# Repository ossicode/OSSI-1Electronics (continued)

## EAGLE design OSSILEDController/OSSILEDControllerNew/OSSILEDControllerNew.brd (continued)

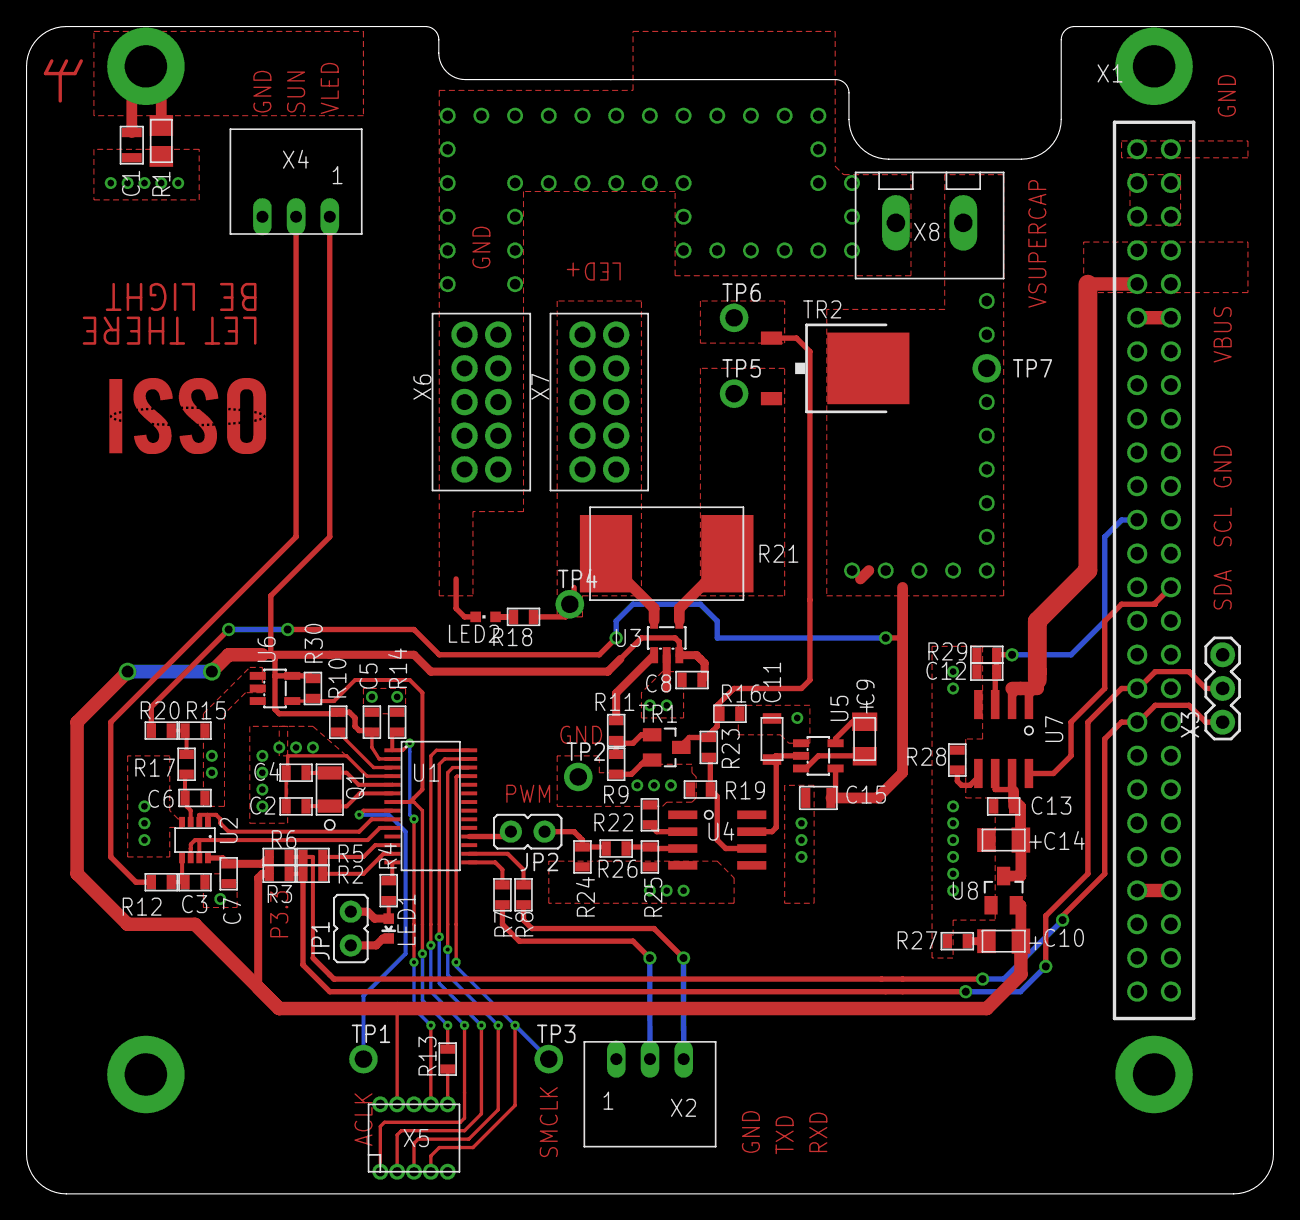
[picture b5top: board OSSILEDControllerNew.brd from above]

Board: 2 copper layers, 94.0 x 88.0 mm, 80 parts (0 on the bottom side), 54 nets.

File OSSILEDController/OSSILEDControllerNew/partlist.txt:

Partlist

Exported from OSSILEDControllerNew.sch at 2013-02-26 ¿ÀÈÄ 1:47:38

EAGLE Version 6.1.0 Copyright (c) 1988-2012 CadSoft

Assembly variant: 

Part     Value                Device             Package              Library  Sheet

C1                            C0805(2012)        C0805(2012)          OSSI     1
C2       12.5pF               C0603(1608)        C0603(1608)          OSSI     2
C3       100nF                C0603(1608)        C0603(1608)          OSSI     2
C4       12.5pF               C0603(1608)        C0603(1608)          OSSI     2
C5       100nF                C0603(1608)        C0603(1608)          OSSI     2
C6       100nF                C0603(1608)        C0603(1608)          OSSI     2
C7       100nF                C0603(1608)        C0603(1608)          OSSI     2
C8       100nF                C0603(1608)        C0603(1608)          OSSI     2
C9       10uF, LDO Tantal 16V C-TANTAL-A         C1206(3216)-A        OSSI     2
C10      10uF, LDO Tantal 16V C-TANTAL-A         C1206(3216)-A        OSSI     2
C11      1206 Cap             C1206(3216)-GCM31  C1206-GCM31          OSSI     2
C12      1uF                  C0603(1608)        C0603(1608)          OSSI     2
C13      100nF                C0603(1608)        C0603(1608)          OSSI     2
C14      10uF, LDO Tantal 16V C-TANTAL-A         C1206(3216)-A        OSSI     2
C15      1uF 0805             C0805(2012)        C0805(2012)          OSSI     2
H1       MOUNT-PAD-ROUND3.2   MOUNT-PAD-ROUND3.2 3.2-PAD-ROUND        OSSI     1
H2       MOUNT-PAD-ROUND3.2   MOUNT-PAD-ROUND3.2 3.2-PAD-ROUND        OSSI     1
H3       MOUNT-PAD-ROUND3.2   MOUNT-PAD-ROUND3.2 3.2-PAD-ROUND        OSSI     1
H4       MOUNT-PAD-ROUND3.2   MOUNT-PAD-ROUND3.2 3.2-PAD-ROUND        OSSI     1
JP1                           JP1Q               JP1                  OSSI     2
JP2                           JP1Q               JP1                  OSSI     2
LED1                          LED0603            LED-0603             SparkFun 2
LED2                          LEDCHIPLED_0603    CHIPLED_0603         led      2
Q1       NX-3215              NX-3215            NX-3215              OSSI     2
R1       511                  RWSL1206           WSL1206              OSSI     1
R2       250                  R0603(1608)        R0603(1608)          OSSI     2
R3       10k                  R0603(1608)        R0603(1608)          OSSI     2
R4       1k                   R0603(1608)        R0603(1608)          OSSI     2
R5       250                  R0603(1608)        R0603(1608)          OSSI     2
R6       10k                  R0603(1608)        R0603(1608)          OSSI     2
R7       4.7k                 R0603(1608)        R0603(1608)          OSSI     2
R8       4.7k                 R0603(1608)        R0603(1608)          OSSI     2
R9       6.2k                 R0603(1608)        R0603(1608)          OSSI     2
R10      TBD                  R0603(1608)        R0603(1608)          OSSI     2
R11      9.1k                 R0603(1608)        R0603(1608)          OSSI     2
R12      1k                   R0603(1608)        R0603(1608)          OSSI     2
R13      4.7k                 R0603(1608)        R0603(1608)          OSSI     2
R14      47k                  R0603(1608)        R0603(1608)          OSSI     2
R15      100k                 R0603(1608)        R0603(1608)          OSSI     2
R16      DNP                  R0603(1608)        R0603(1608)          OSSI     2
R17      1k                   R0603(1608)        R0603(1608)          OSSI     2
R18      1.5k                 R0603(1608)        R0603(1608)          OSSI     2
R19      2.2k                 R0603(1608)        R0603(1608)          OSSI     2
R20      100k                 R0603(1608)        R0603(1608)          OSSI     2
R21      0.005, 2W RSENSE     RWSR2              R4527(12070)         OSSI     2
R22      1.1k                 R0603(1608)        R0603(1608)          OSSI     2
R23      100k                 R0603(1608)        R0603(1608)          OSSI     2
R24      100k                 R0603(1608)        R0603(1608)          OSSI     2
R25                           R0603(1608)        R0603(1608)          OSSI     2
R26      1.5k                 R0603(1608)        R0603(1608)          OSSI     2
R27      0                    R0603(1608)        R0603(1608)          OSSI     2
R28      TBD                  R0603(1608)        R0603(1608)          OSSI     2
R29      100k                 R0603(1608)        R0603(1608)          OSSI     2
R30      100k                 R0603(1608)        R0603(1608)          OSSI     2
TP1      TP                   TP                 TP-13                OSSI     2
TP2      TP                   TP                 TP-13                OSSI     2
TP3      TP                   TP                 TP-13                OSSI     2
TP4      TP                   TP                 TP-13                OSSI     2
TP5      TP                   TP                 TP-13                OSSI     2
TP6      TP                   TP                 TP-13                OSSI     2
TP7      TP                   TP                 TP-13                OSSI     2
TR1      FDV301N              FDV301N            SOT23                OSSI     2
TR2      FDD8896              FDD8896            TO252                OSSI     2
U1       MSP430F2132          MSP430F2132        PW28                 OSSI     2
U2       OPA2347              OPA2347            SOT23-8DCN           OSSI     2
U3       MAX4376              MAX4376            SOT23-5DBV           OSSI     2
U4       LM7321               LM7321             SO8                  OSSI     2
U5       MAX1682              MAX1682            SOT23-5DBV           OSSI     2
U6       TPS3838              TPS3838            SOT23-5DBV           OSSI     2
U7       MAX890L              MAX890L            SO8                  OSSI     2
U8       MCP1700_SOT23        MCP1700_SOT23      SOT23                OSSI     2
X1       ESQ-126-38-G-D       ESQ-126-38-G-D     ESQ-126-XX-X-D       OSSI     1
X2       5268-03              5268-03            5268-03              OSSI     2
X3                            M03PTH             1X03                 OSSI     2
X4       5268-03              5268-03            5268-03              OSSI     2
X5       JTAG10PINMINI-H      JTAG10PINMINI-H    M50-3200545          OSSI     2
X6       ICCON_POWERCON       ICCON_POWERCON     ICCON6643220-1       OSSI     2
X7       ICCON_POWERCON       ICCON_POWERCON     ICCON6643220-1       OSSI     2
X8       WEIDMULLER           WEIDMULLER         WEIDMULLER1760490000 OSSI     2

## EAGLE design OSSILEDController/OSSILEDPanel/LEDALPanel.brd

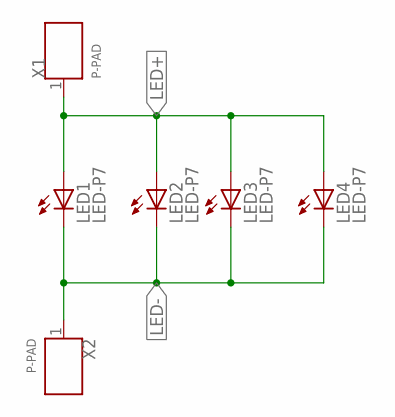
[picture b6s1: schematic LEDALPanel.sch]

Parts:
LED1, LED2, LED3, LED4: LED-P7; P7
X1, X2: P-PAD

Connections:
LED+: LED1.A, LED2.A, LED3.A, LED4.A, X1.1
LED-: LED1.C, LED2.C, LED3.C, LED4.C, X2.1

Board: 2 copper layers, 6 parts (0 on the bottom side), 2 nets, no tracks yet.

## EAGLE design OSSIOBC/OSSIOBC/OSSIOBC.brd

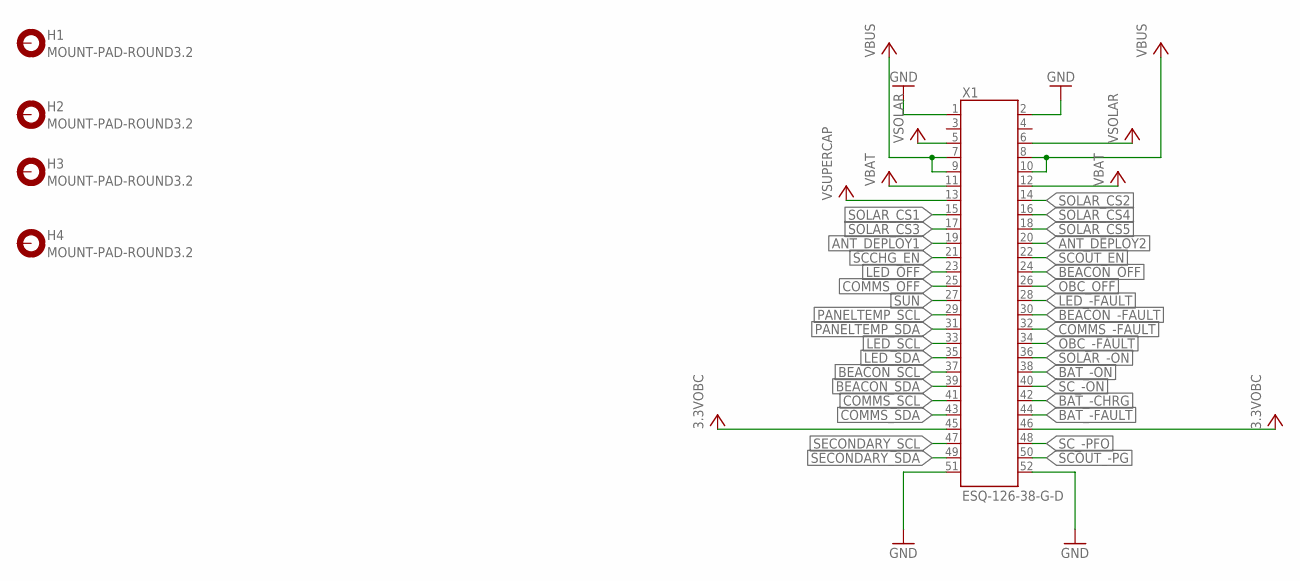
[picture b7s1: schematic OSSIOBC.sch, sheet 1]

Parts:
H1, H2, H3, H4: MOUNT-PAD-ROUND3.2; 3.2-PAD-ROUND
X1: ESQ-126-38-G-D; ESQ-126-XX-X-D

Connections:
3.3VOBC: X1.45, X1.46; also elsewhere on the board
ANT_DEPLOY1: X1.19; also elsewhere on the board
ANT_DEPLOY2: X1.20; also elsewhere on the board
BAT_-CHRG: X1.42; also elsewhere on the board
BAT_-FAULT: X1.44; also elsewhere on the board
BAT_-ON: X1.38; also elsewhere on the board
BEACON_-FAULT: X1.30; also elsewhere on the board
BEACON_OFF: X1.24; also elsewhere on the board
BEACON_SCL: X1.37; also elsewhere on the board
BEACON_SDA: X1.39; also elsewhere on the board
COMMS_-FAULT: X1.32; also elsewhere on the board
COMMS_OFF: X1.25; also elsewhere on the board
COMMS_SCL: X1.41; also elsewhere on the board
COMMS_SDA: X1.43; also elsewhere on the board
GND: X1.1, X1.2, X1.51, X1.52; also elsewhere on the board
LED_-FAULT: X1.28; also elsewhere on the board
LED_OFF: X1.23; also elsewhere on the board
LED_SCL: X1.33; also elsewhere on the board
LED_SDA: X1.35; also elsewhere on the board
OBC_-FAULT: X1.34; also elsewhere on the board
OBC_OFF: X1.26; also elsewhere on the board
PANELTEMP_SCL: X1.29; also elsewhere on the board
PANELTEMP_SDA: X1.31; also elsewhere on the board
SCCHG_EN: X1.21; also elsewhere on the board
SCOUT_-PG: X1.50; also elsewhere on the board
SCOUT_EN: X1.22; also elsewhere on the board
SC_-ON: X1.40; also elsewhere on the board
SC_-PFO: X1.48; also elsewhere on the board
SECONDARY_SCL: X1.47; also elsewhere on the board
SECONDARY_SDA: X1.49; also elsewhere on the board
SOLAR_-ON: X1.36; also elsewhere on the board
SOLAR_CS1: X1.15; also elsewhere on the board
SOLAR_CS2: X1.14; also elsewhere on the board
SOLAR_CS3: X1.17; also elsewhere on the board
SOLAR_CS4: X1.16; also elsewhere on the board
SOLAR_CS5: X1.18; also elsewhere on the board
SUN: X1.27; also elsewhere on the board
VBAT: X1.11, X1.12; also elsewhere on the board
VBUS: X1.7, X1.8, X1.9, X1.10; also elsewhere on the board
VSOLAR: X1.5, X1.6; also elsewhere on the board
VSUPERCAP: X1.13; also elsewhere on the board

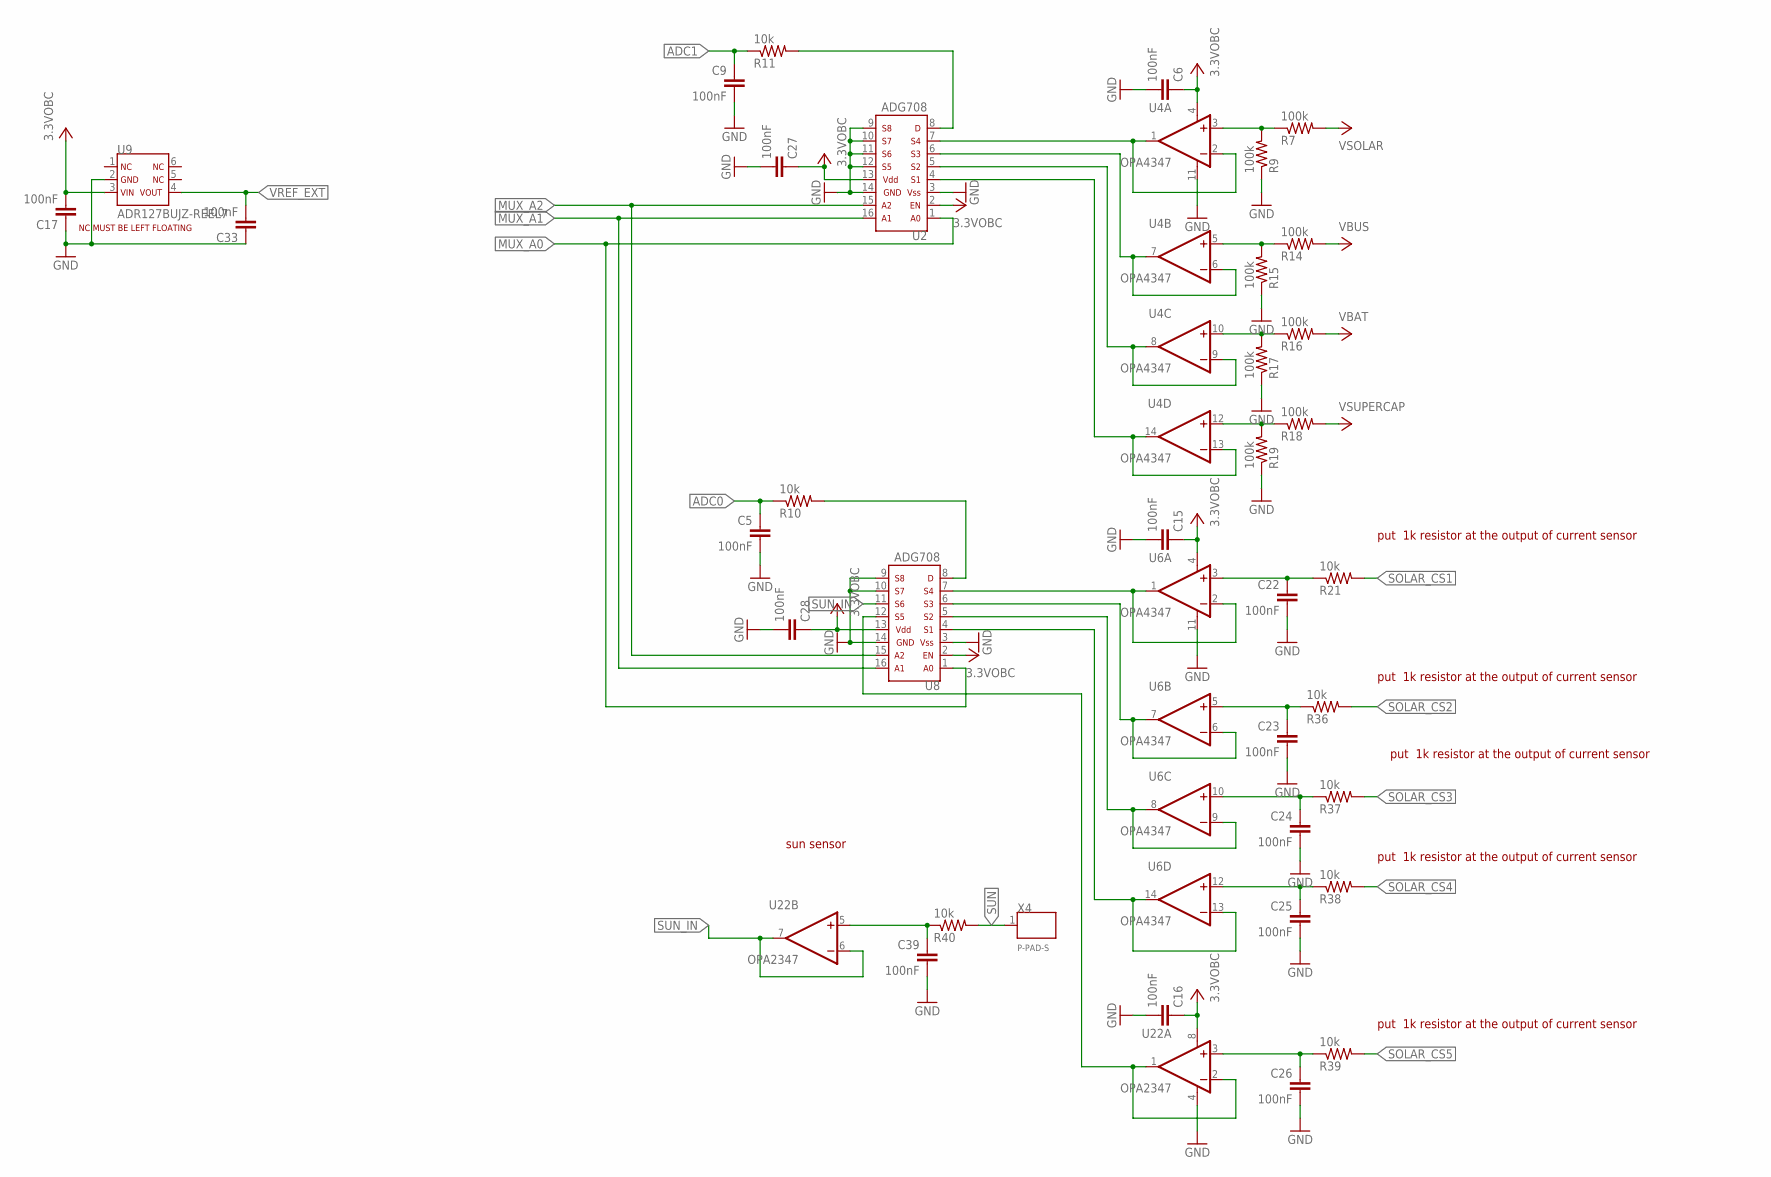
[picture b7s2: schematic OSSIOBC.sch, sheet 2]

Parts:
C5, C6, C9, C15, C16, C17, C22, C23, C24, C25, C26, C27, C28, C33, C39: 100nF; C0603(1608)
R7, R9, R14, R15, R16, R17, R18, R19: 100k; R0603(1608)
R10, R11, R21, R36, R37, R38, R39, R40: 10k; R0603(1608)
U2, U8: ADG708; TSSOP16-RU
U4, U6: OPA4347; TSSOP14-PW
U9: ADR127BUJZ-REEL7; TSOT-6UJ-6
U22: OPA2347; SOT23-8DCN
X4: P-PAD-S

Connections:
3.3VOBC: C6.1, C15.1, C16.1, C17.2, C27.1, C28.1, U2.2, U2.13, U4.4 (V+), U6.4 (V+), U8.2, U8.13, U9.3, U22.8 (V+); also elsewhere on the board
ADC0: C5.1, R10.1; also elsewhere on the board
ADC1: C9.1, R11.1; also elsewhere on the board
GND: C5.2, C6.2, C9.2, C15.2, C16.2, C17.1, C22.2, C23.2, C24.2, C25.2, C26.2, C27.2, C28.2, C33.1, C39.2, R9.1, R15.1, R17.1, R19.1, U2.3, U2.9, U2.10, U2.11, U2.12, U2.14, U4.11 (V-), U6.11 (V-), U8.3, U8.9, U8.10, U8.14, U9.2, U22.4 (V-); also elsewhere on the board
MUX_A0: U2.1, U8.1; also elsewhere on the board
MUX_A1: U2.16, U8.16; also elsewhere on the board
MUX_A2: U2.15, U8.15; also elsewhere on the board
unnamed: R7.1, R9.2, U4.3 (+IN)
unnamed: U2.7, U4.1 (OUT), U4.2 (-IN)
unnamed: U2.6, U4.6 (-IN), U4.7 (OUT)
unnamed: U2.5, U4.8 (OUT), U4.9 (-IN)
unnamed: U2.4, U4.13 (-IN), U4.14 (OUT)
unnamed: U6.1 (OUT), U6.2 (-IN), U8.7
unnamed: U6.6 (-IN), U6.7 (OUT), U8.6
unnamed: R14.1, R15.2, U4.5 (+IN)
unnamed: R16.1, R17.2, U4.10 (+IN)
unnamed: R18.1, R19.2, U4.12 (+IN)
unnamed: R11.2, U2.8
unnamed: U6.8 (OUT), U6.9 (-IN), U8.5
unnamed: R10.2, U8.8
unnamed: U6.13 (-IN), U6.14 (OUT), U8.4
unnamed: U8.12, U22.1 (OUT), U22.2 (-IN)
unnamed: C22.1, R21.1, U6.3 (+IN)
unnamed: C23.1, R36.1, U6.5 (+IN)
unnamed: C24.1, R37.1, U6.10 (+IN)
unnamed: C25.1, R38.1, U6.12 (+IN)
unnamed: C26.1, R39.1, U22.3 (+IN)
unnamed: C39.1, R40.1, U22.5 (+IN)
SOLAR_CS1: R21.2; also elsewhere on the board
SOLAR_CS2: R36.2; also elsewhere on the board
SOLAR_CS3: R37.2; also elsewhere on the board
SOLAR_CS4: R38.2; also elsewhere on the board
SOLAR_CS5: R39.2; also elsewhere on the board
SUN: R40.2, X4.1; also elsewhere on the board
SUN_IN: U8.11, U22.6 (-IN), U22.7 (OUT)
VBAT: R16.2; also elsewhere on the board
VBUS: R14.2; also elsewhere on the board
VREF_EXT: C33.2, U9.4; also elsewhere on the board
VSOLAR: R7.2; also elsewhere on the board
VSUPERCAP: R18.2; also elsewhere on the board

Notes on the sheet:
put 1k resistor at the output of current sensor
sun sensor

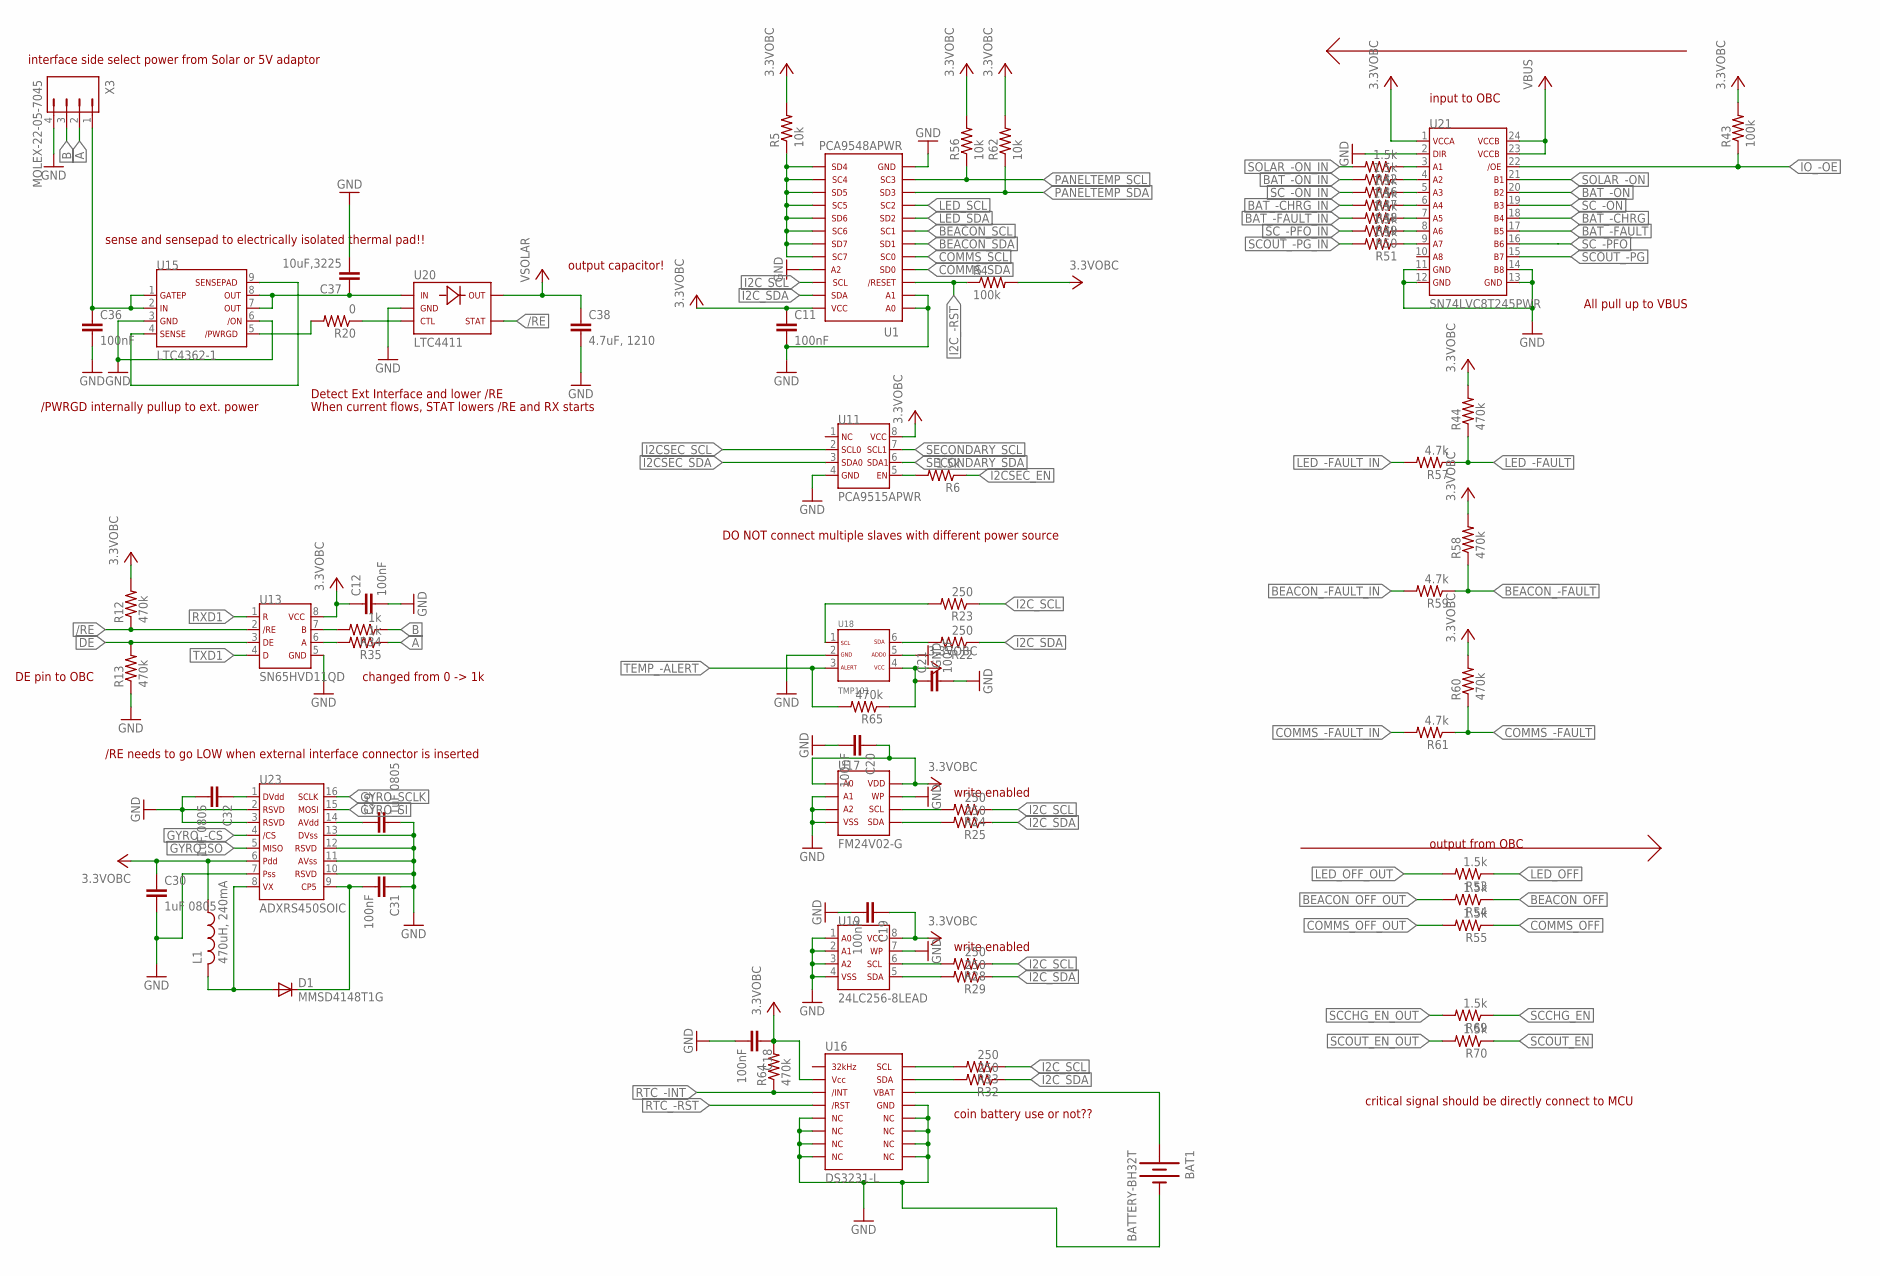
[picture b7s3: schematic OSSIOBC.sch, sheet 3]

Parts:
BAT1: BATTERY-BH32T; BH32T-C-G
C11, C12, C18, C19, C20, C21, C31, C36: 100nF; C0603(1608)
C29, C30, C32: 1uF 0805; C0805(2012)
C37: 10uF,3225; C1210-GCM32
C38: 4.7uF, 1210; C1206-GCM31
D1: MMSD4148T1G; SOD-123
L1: 470uH, 240mA; L(2220)
R4, R43: 100k; R0603(1608)
R5, R56, R62: 10k; R0603(1608)
R6, R42, R46, R47, R48, R49, R50, R51, R53, R54, R55, R69, R70: 1.5k; R0603(1608)
R12, R13, R44, R58, R60, R64, R65: 470k; R0603(1608)
R20: 0; R0603(1608)
R22, R23, R24, R25, R28, R29, R32, R33: 250; R0603(1608)
R34, R35: 1k; R0603(1608)
R57, R59, R61: 4.7k; R0603(1608)
U1: PCA9548APWR; TSSOP-24-PW
U11: PCA9515APWR; TSSOP-8
U13: SN65HVD11QD; SO8
U15: LTC4362-1; DFN8-2X3
U16: DS3231-L; SO16L
U17: FM24V02-G; SO8
U18: TMP101; SOT23-6DBV
U19: 24LC256-8LEAD; SO08-208
U20: LTC4411; TSOT23-5
U21: SN74LVC8T245PWR; PW_R-PDSO-G24
U23: ADXRS450SOIC; SOIC-16CAV
X3: MOLEX-22-05-7045; 22-05-7045

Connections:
3.3VOBC: C11.1, C12.1, C18.1, C19.1, C20.1, C21.1, C30.1, L1.P$1 (1), R4.2, R5.2, R12.2, R43.2, R44.2, R56.2, R58.2, R60.2, R62.2, R64.2, R65.1, U1.24, U11.8, U13.8, U16.2, U17.1 (A0), U17.8 (VDD), U18.4, U19.8, U21.1, U23.6; also elsewhere on the board
/RE: R12.1, U13.2, U20.P$4
A: R35.1, X3.2
B: R34.1, X3.3
BAT_-CHRG: U21.18; also elsewhere on the board
BAT_-CHRG_IN: R48.2; also elsewhere on the board
BAT_-FAULT: U21.17; also elsewhere on the board
BAT_-FAULT_IN: R49.2; also elsewhere on the board
BAT_-ON: U21.20; also elsewhere on the board
BAT_-ON_IN: R46.2; also elsewhere on the board
BEACON_-FAULT: R58.1, R59.1; also elsewhere on the board
BEACON_-FAULT_IN: R59.2; also elsewhere on the board
BEACON_OFF: R54.1; also elsewhere on the board
BEACON_OFF_OUT: R54.2; also elsewhere on the board
BEACON_SCL: U1.7; also elsewhere on the board
BEACON_SDA: U1.6; also elsewhere on the board
COMMS_-FAULT: R60.1, R61.1; also elsewhere on the board
COMMS_-FAULT_IN: R61.2; also elsewhere on the board
COMMS_OFF: R55.1; also elsewhere on the board
COMMS_OFF_OUT: R55.2; also elsewhere on the board
COMMS_SCL: U1.5; also elsewhere on the board
COMMS_SDA: U1.4; also elsewhere on the board
DE: R13.2, U13.3; also elsewhere on the board
GND: BAT1.N (-), C11.2, C12.2, C18.2, C19.2, C20.2, C21.2, C29.2, C30.2, C31.1, C32.2, C36.2, C37.P$2 (2), C38.P$2 (2), R13.1, U1.1, U1.2, U1.12, U1.21, U11.4, U13.5, U15.3, U15.6, U16.5, U16.6, U16.7, U16.8, U16.9, U16.10, U16.11, U16.12, U16.13, U17.2 (A1), U17.3 (A2), U17.4 (VSS), U17.7 (WP), U18.2, U18.5, U19.1, U19.2, U19.3, U19.4, U19.7, U20.P$2, U21.2, U21.11, U21.12, U21.13, U21.14, U23.2, U23.3, U23.7, U23.10, U23.11, U23.12, U23.13, X3.4; also elsewhere on the board
GYRO_-CS: U23.4; also elsewhere on the board
GYRO_SCLK: U23.16; also elsewhere on the board
GYRO_SI: U23.15; also elsewhere on the board
GYRO_SO: U23.5; also elsewhere on the board
I2CSEC_EN: R6.1; also elsewhere on the board
I2CSEC_SCL: U11.2; also elsewhere on the board
I2CSEC_SDA: U11.3; also elsewhere on the board
I2C_-RST: R4.1, U1.3; also elsewhere on the board
I2C_SCL: R23.1, R24.1, R28.1, R33.1, U1.22; also elsewhere on the board
I2C_SDA: R22.1, R25.1, R29.1, R32.1, U1.23; also elsewhere on the board
IO_-OE: R43.1, U21.22; also elsewhere on the board
LED_-FAULT: R44.1, R57.1; also elsewhere on the board
LED_-FAULT_IN: R57.2; also elsewhere on the board
LED_OFF: R53.1; also elsewhere on the board
LED_OFF_OUT: R53.2; also elsewhere on the board
LED_SCL: U1.9; also elsewhere on the board
LED_SDA: U1.8; also elsewhere on the board
unnamed: C36.1, U15.1, U15.2, X3.1
unnamed: R32.2, U16.15
unnamed: R34.2, U13.7
unnamed: R33.2, U16.16
unnamed: R5.1, U1.13, U1.14, U1.15, U1.16, U1.17, U1.18, U1.19, U1.20
unnamed: R35.2, U13.6
unnamed: C32.1, U23.1
unnamed: R29.2, U19.5
unnamed: R28.2, U19.6
unnamed: R25.2, U17.5 (SDA)
unnamed: R24.2, U17.6 (SCL)
unnamed: R22.2, U18.6
unnamed: R23.2, U18.1
unnamed: C37.P$1 (1), U15.7, U15.8, U20.P$1
unnamed: U15.4, U15.9
unnamed: R6.2, U11.5
unnamed: R20.2, U15.5
unnamed: C29.1, U23.14
unnamed: R20.1, U20.P$3
unnamed: R48.1, U21.6
unnamed: R49.1, U21.7
unnamed: R50.1, U21.8
unnamed: R51.1, U21.9
unnamed: BAT1.P (+), U16.14
unnamed: R47.1, U21.5
unnamed: R46.1, U21.4
unnamed: R42.1, U21.3
unnamed: D1.A, L1.P$2 (2), U23.8
unnamed: C31.2, D1.C, U23.9
PANELTEMP_SCL: R56.1, U1.11; also elsewhere on the board
PANELTEMP_SDA: R62.1, U1.10; also elsewhere on the board
RTC_-INT: R64.1, U16.3; also elsewhere on the board
RTC_-RST: U16.4; also elsewhere on the board
RXD1: U13.1; also elsewhere on the board
SCCHG_EN: R69.1; also elsewhere on the board
SCCHG_EN_OUT: R69.2; also elsewhere on the board
SCOUT_-PG: U21.15; also elsewhere on the board
SCOUT_-PG_IN: R51.2; also elsewhere on the board
SCOUT_EN: R70.1; also elsewhere on the board
SCOUT_EN_OUT: R70.2; also elsewhere on the board
SC_-ON: U21.19; also elsewhere on the board
SC_-ON_IN: R47.2; also elsewhere on the board
SC_-PFO: U21.16; also elsewhere on the board
SC_-PFO_IN: R50.2; also elsewhere on the board
SECONDARY_SCL: U11.7; also elsewhere on the board
SECONDARY_SDA: U11.6; also elsewhere on the board
SOLAR_-ON: U21.21; also elsewhere on the board
SOLAR_-ON_IN: R42.2; also elsewhere on the board
TEMP_-ALERT: R65.2, U18.3; also elsewhere on the board
TXD1: U13.4; also elsewhere on the board
VBUS: U21.23, U21.24; also elsewhere on the board
VSOLAR: C38.P$1 (1), U20.P$5; also elsewhere on the board

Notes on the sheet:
DO NOT connect multiple slaves with different power source
/RE needs to go LOW when external interface connector is inserted
Detect Ext Interface and lower /RE
coin battery use or not??
sense and sensepad to electrically isolated thermal pad!!
/PWRGD internally pullup to ext. power
When current flows, STAT lowers /RE and RX starts
interface side select power from Solar or 5V adaptor
DE pin to OBC
output capacitor!
input to OBC
output from OBC
All pull up to VBUS
write enabled
critical signal should be directly connect to MCU
changed from 0 -> 1k

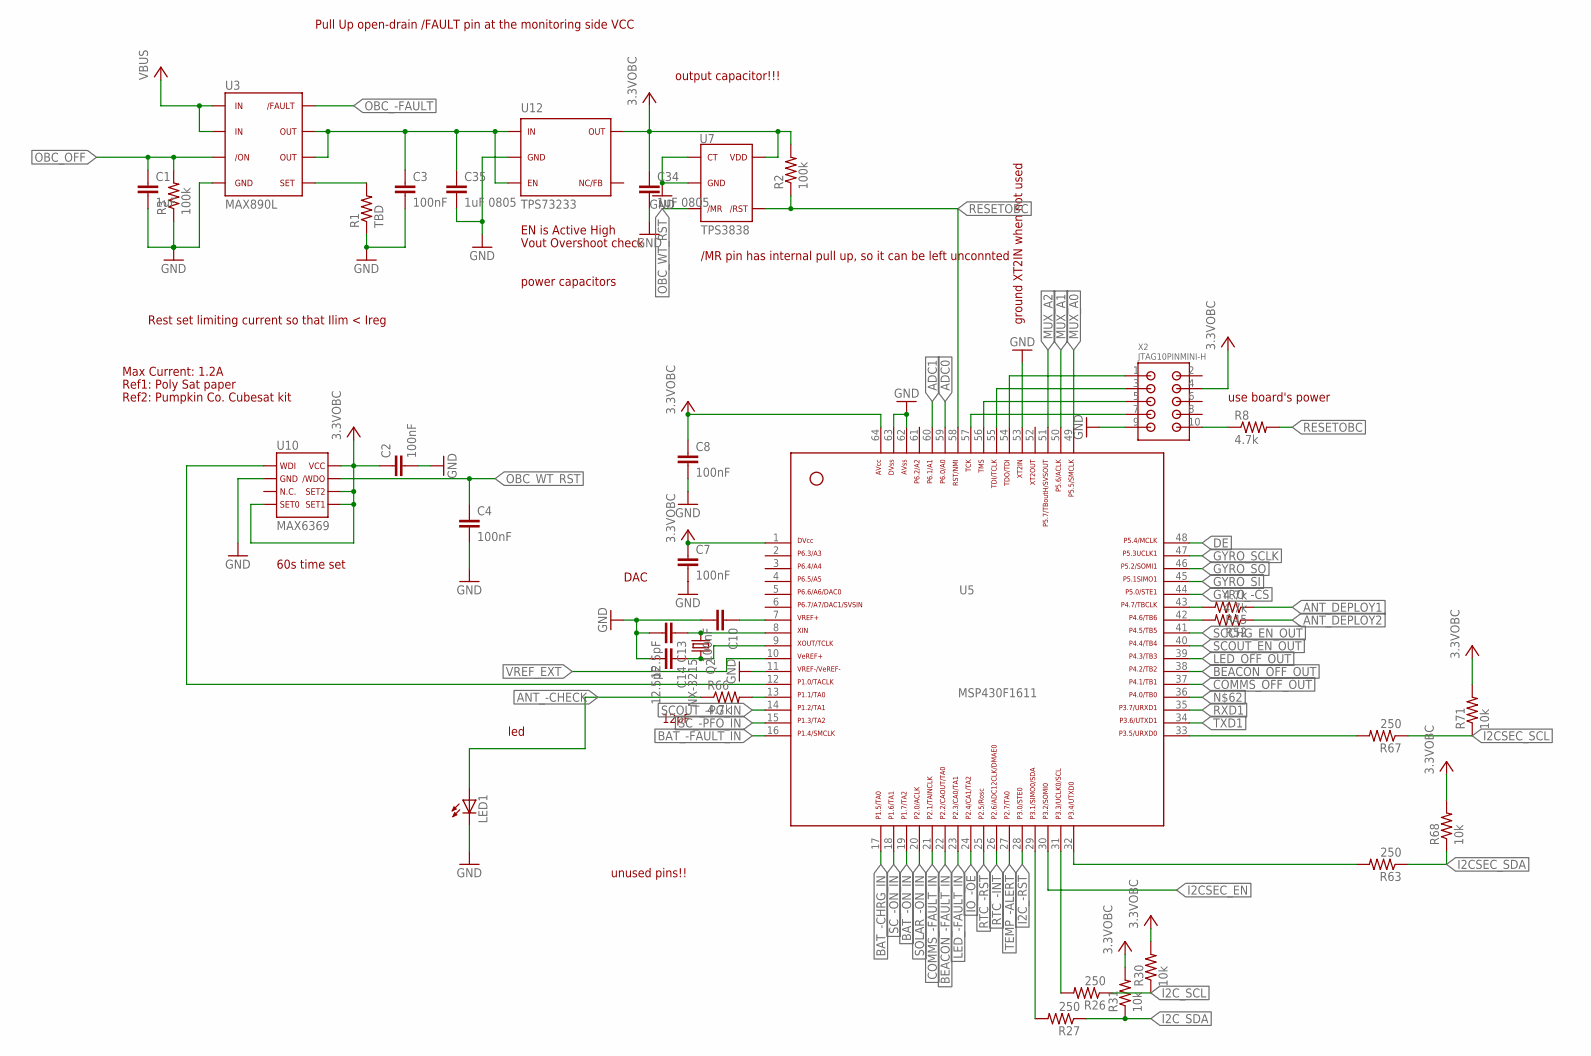
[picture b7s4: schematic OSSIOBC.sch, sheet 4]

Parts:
C1: 1uF; C0603(1608)
C2, C3, C4, C7, C8, C10: 100nF; C0603(1608)
C13, C14: 12.5pF; C0603(1608)
C34, C35: 1uF 0805; C0805(2012)
LED1: LED0603; LED-0603
Q2: NX-3215
R1: TBD; R0603(1608)
R2, R3: 100k; R0603(1608)
R8, R45, R52, R66: 4.7k; R0603(1608)
R26, R27, R63, R67: 250; R0603(1608)
R30, R31, R68, R71: 10k; R0603(1608)
U3: MAX890L; SO8
U5: MSP430F1611; PM/PAG64
U7: TPS3838; SOT23-5DBV
U10: MAX6369; SOT23-8
U12: TPS73233; SOT23-5DBV
X2: JTAG10PINMINI-H; M50-3200545

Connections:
3.3VOBC: C2.1, C7.1, C8.1, C34.1, R2.2, R30.2, R31.2, R68.2, R71.2, U5.1, U5.64, U7.5, U10.4, U10.5, U10.6, U10.8, U12.5, X2.4; also elsewhere on the board
ADC0: U5.59; also elsewhere on the board
ADC1: U5.60; also elsewhere on the board
ANT_-CHECK: LED1.A, R66.1
ANT_DEPLOY1: R45.1; also elsewhere on the board
ANT_DEPLOY2: R52.1; also elsewhere on the board
BAT_-CHRG_IN: U5.17; also elsewhere on the board
BAT_-FAULT_IN: U5.16; also elsewhere on the board
BAT_-ON_IN: U5.19; also elsewhere on the board
BEACON_-FAULT_IN: U5.22; also elsewhere on the board
BEACON_OFF_OUT: U5.38; also elsewhere on the board
COMMS_-FAULT_IN: U5.21; also elsewhere on the board
COMMS_OFF_OUT: U5.37; also elsewhere on the board
DE: U5.48; also elsewhere on the board
GND: C1.2, C2.2, C3.2, C4.2, C7.2, C8.2, C10.2, C13.2, C14.2, C34.2, C35.2, LED1.C, R1.1, R3.1, U3.4, U5.11, U5.53, U5.62, U5.63, U7.1, U7.2, U10.2, U12.2, X2.9; also elsewhere on the board
GYRO_-CS: U5.44; also elsewhere on the board
GYRO_SCLK: U5.47; also elsewhere on the board
GYRO_SI: U5.45; also elsewhere on the board
GYRO_SO: U5.46; also elsewhere on the board
I2CSEC_EN: U5.30; also elsewhere on the board
I2CSEC_SCL: R67.1, R71.1; also elsewhere on the board
I2CSEC_SDA: R63.1, R68.1; also elsewhere on the board
I2C_-RST: U5.28; also elsewhere on the board
I2C_SCL: R26.1, R30.1; also elsewhere on the board
I2C_SDA: R27.1, R31.1; also elsewhere on the board
IO_-OE: U5.24; also elsewhere on the board
LED_-FAULT_IN: U5.23; also elsewhere on the board
LED_OFF_OUT: U5.39; also elsewhere on the board
MUX_A0: U5.49; also elsewhere on the board
MUX_A1: U5.50; also elsewhere on the board
MUX_A2: U5.51; also elsewhere on the board
unnamed: U5.12, U10.1
unnamed: C13.1, Q2.1, U5.8
unnamed: C14.1, Q2.2, U5.9
unnamed: R1.2, U3.5
unnamed: C10.1, U5.7
unnamed: U5.57, X2.7
unnamed: U5.56, X2.5
unnamed: U5.55, X2.3
unnamed: U5.54, X2.1
unnamed: R8.1, X2.10
unnamed: R66.2, U5.13
unnamed: R45.2, U5.43
unnamed: R52.2, U5.42
unnamed: R67.2, U5.33
unnamed: R27.2, U5.29
unnamed: R26.2, U5.31
unnamed: R63.2, U5.32
unnamed: C3.1, C35.1, U3.6, U3.7, U12.1, U12.3
OBC_-FAULT: U3.8; also elsewhere on the board
OBC_OFF: C1.1, R3.2, U3.3; also elsewhere on the board
OBC_WT_RST: C4.1, U7.3, U10.7
RESETOBC: R2.1, R8.2, U5.58, U7.4
RTC_-INT: U5.26; also elsewhere on the board
RTC_-RST: U5.25; also elsewhere on the board
RXD1: U5.35; also elsewhere on the board
SCCHG_EN_OUT: U5.41; also elsewhere on the board
SCOUT_-PG_IN: U5.14; also elsewhere on the board
SCOUT_EN_OUT: U5.40; also elsewhere on the board
SC_-ON_IN: U5.18; also elsewhere on the board
SC_-PFO_IN: U5.15; also elsewhere on the board
SOLAR_-ON_IN: U5.20; also elsewhere on the board
TEMP_-ALERT: U5.27; also elsewhere on the board
TXD1: U5.34; also elsewhere on the board
VBUS: U3.1, U3.2; also elsewhere on the board
VREF_EXT: U5.10; also elsewhere on the board

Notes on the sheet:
60s time set
12pF
use board's power
DAC
Rest set limiting current so that Ilim < Ireg
Pull Up open-drain /FAULT pin at the monitoring side VCC
Max Current: 1.2A
Ref1: Poly Sat paper
Ref2: Pumpkin Co. Cubesat kit
EN is Active High
/MR pin has internal pull up, so it can be left unconnted
Vout Overshoot check
power capacitors
output capacitor!!!
unused pins!!
ground XT2IN when not used
led
